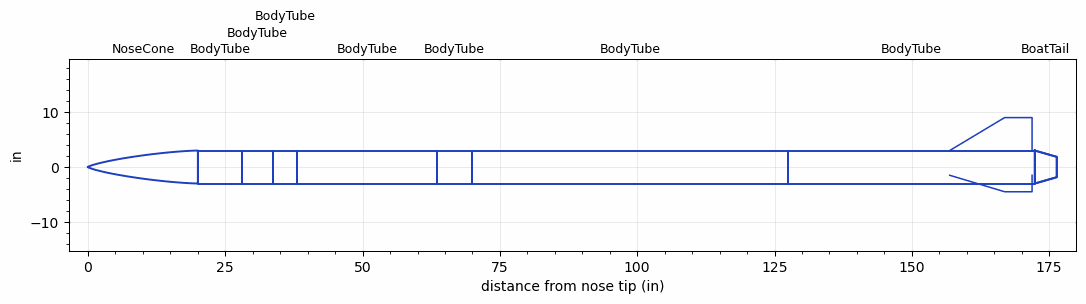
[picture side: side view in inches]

<RASAeroDocument>
 <FileVersion>2</FileVersion>
 <RocketDesign>
  <NoseCone>
   <Length>20</Length>
   <Diameter>6</Diameter>
   <Shape>Von Karman Ogive</Shape>
   <Location>0</Location>
  </NoseCone>
  <BodyTube>
   <Length>8</Length>
   <Diameter>6</Diameter>
   <Location>20</Location>
  </BodyTube>
  <BodyTube>
   <Length>5.7</Length>
   <Diameter>6</Diameter>
   <Location>28</Location>
  </BodyTube>
  <BodyTube>
   <Length>4.31</Length>
   <Diameter>6</Diameter>
   <Location>33.7</Location>
  </BodyTube>
  <BodyTube>
   <Length>25.5</Length>
   <Diameter>6</Diameter>
   <Location>38.01</Location>
  </BodyTube>
  <BodyTube>
   <Length>6.38</Length>
   <Diameter>6</Diameter>
   <Location>63.51</Location>
  </BodyTube>
  <BodyTube>
   <Length>57.56</Length>
   <Diameter>6</Diameter>
   <Location>69.89</Location>
  </BodyTube>
  <BodyTube>
   <Length>44.95</Length>
   <Diameter>6</Diameter>
   <Location>127.45</Location>
   <BoattailLength>4</BoattailLength>
   <BoattailRearDiameter>3.706</BoattailRearDiameter>
   <Fin>
    <Count>3</Count>
    <Chord>15</Chord>
    <Span>6</Span>
    <SweepDistance>10</SweepDistance>
    <TipChord>5</TipChord>
    <Thickness>0.5</Thickness>
    <Location>15.5</Location>
    <AirfoilSection>Double Wedge</AirfoilSection>
    <FX1>5</FX1>
    <FX3>1</FX3>
   </Fin>
  </BodyTube>
  <BoatTail>
   <Length>4</Length>
   <Diameter>6</Diameter>
   <RearDiameter>3.706</RearDiameter>
   <Location>172.4</Location>
  </BoatTail>
  <Surface>Smooth Paint</Surface>
  <ModifiedBarrowman>True</ModifiedBarrowman>
  <Turbulence>False</Turbulence>
  <UseBooster1>False</UseBooster1>
  <UseBooster2>False</UseBooster2>
 </RocketDesign>
 <LaunchSite>
  <Altitude>295</Altitude>
  <Pressure>30</Pressure>
  <RodAngle>0</RodAngle>
  <RodLength>30</RodLength>
  <Temperature>74</Temperature>
  <WindSpeed>10</WindSpeed>
 </LaunchSite>
 <Recovery>
  <Altitude1>1000</Altitude1>
  <Altitude2>1000</Altitude2>
  <DeviceType1>None</DeviceType1>
  <DeviceType2>None</DeviceType2>
  <Event1>False</Event1>
  <Event2>False</Event2>
  <Size1>1</Size1>
  <Size2>1</Size2>
  <EventType1>None</EventType1>
  <EventType2>None</EventType2>
  <CD1>1.33</CD1>
  <CD2>1.33</CD2>
 </Recovery>
 <SimulationList>
  <Simulation>
   <SustainerEngine>EngineTestDR  (TAMUSRT)</SustainerEngine>
   <SustainerLaunchWt>124.29</SustainerLaunchWt>
   <SustainerNozzleDiameter>2.84</SustainerNozzleDiameter>
   <SustainerCG>110.18</SustainerCG>
   <SustainerIgnitionDelay>0</SustainerIgnitionDelay>
   <Booster1SeparationDelay>0</Booster1SeparationDelay>
   <Booster1IgnitionDelay>0</Booster1IgnitionDelay>
   <IncludeBooster1>False</IncludeBooster1>
   <Booster2Delay>0</Booster2Delay>
   <IncludeBooster2>False</IncludeBooster2>
   <TimetoApogee>55.70666</TimetoApogee>
   <MaxAltitude>45396.53</MaxAltitude>
   <MaxVelocity>1677.034</MaxVelocity>
  </Simulation>
 </SimulationList>
</RASAeroDocument>
